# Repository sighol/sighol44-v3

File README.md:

# Sighol-44 v3

# Installation

Install both `kicad` and `kicad-library` from the OS package repository.

Remember to add the [marbastlib](https://github.com/ebastler/marbastlib) symbol and footprints library.
Check the github page for installation instructions.

Also install the `Fabrication toolkit` from the official KiCad repository.
Search for `JLC` in the plugins tab.

# Inkscape edge cut tutorial

## Export SVG from KiCad
- In KiCad, *File* -> *Print*
- Select the Fab, Silkscreen, and User.Drawings layers.
- Then print as SVG

## Convert SVG to Bitmap to make it easier to work with. (optional)
- Open the SVG in inkscape.
- Open Edit ->, Preference, and select the *Imported Images* tab.
- Change the Craete resolution to about 500 dpi and close the preferences window.
- Then select (S) the white background and delete it.
- Then select (S) everything else.
- Click on Edit -> Make a Bitmap copy.
- Then move the bitmap copy to the center of the screen and delete all the other paths

Another alternative is to create a new layer, and move all the paths into this layer.
Snapping will work better when drawing the initial bezier curve, but I don't think it is worth it.

## Draw outline

- Use the **Pen Tool** (B) to draw an outline around the board. Use straight lines.b
- Hold down CTRL to draw straight lines.
- Move around the canvas by holding down the middle mouse button.
- After you have completed the outline, you can use the Node Tool (N) to delete nodes that are redundant. Select the node and use the **Delete** key.
- Delete bezier curve handles by holding control and left clicking on them.
- Add bezier curve handles by holding control and left clicking on a node.
- Double click on the curve to add a new node.
- Show the bezier handles by toggling a button to the right of the X and Y text boxes.
- The X and Y text boxes can also be used to place the nodes.

## Path effects
- Make sure none of the nodes have bezier curve handles.
- First create an offset of around 1mm.
- Then create a corner of around 1mm.
- Then you can customize the corners using the Node Tool (N).
- Make sure the radiuses you customize are symmetric and equal. You _will_ notice.
- For the thumb keys, it is best to have the biggest possible radius (to the center of the switch).

## Exporting SVG for KiCad

- File -> Export (Ctrl+Shift+E)
- Select the output directory and file. Should be `output_export.svg`.
- Toggle **Export Selected Only**.
- Select the outline (S).
- Click on the **Export** button.

## Import into KiCad

- File -> Import -> Graphics
- Use Import scale 1.33 and set layer to Edge.Cuts, and click OK.
- It is useful to select the outline and press M to move it around using the arrow keys. Press ENTER to confirm.
- You will have to iterate. If you create a big fill zone (select F.Cu and fill with ground), and then fill with **B**, you can use that as a guide when deleting and adding back the new edge cut.
- Alternatively, after placing it, notice

It is easy to place the new export on the of the previous export and then delete the previous, for placement.

## Tips and tricks with design

- The bigger the outline, the easier it will be to place rubber feet so that it doesn't wobble.
- Place the grid on the top-left key. `Place` -> `Grid`.
- Guideline: Horizontal traces are blue. Vertical traces are red.
- In **PCB Editor**:
    - F8 to apply from schematics
    - B to build fill zones.
    - Ctrl+Shift+F to import graphics.
    - Top Copper **PgUp**
    - Bottom Copper **PgDown**
    - V: Toggle top and bottom copper layer
    - Tools -> Update Footprints from Library: Take them all!
    - Text fields support [variables substitiution](https://docs.kicad.org/master/id/eeschema/eeschema_advanced.html#:~:text=KiCad%20supports%20text%20variables%2C%20which,schematic%20or%20board%20setup%20dialogs.)
    - D: Drag component line or track. (You can also drag the tracks.)
    - G: Drag component node or track.

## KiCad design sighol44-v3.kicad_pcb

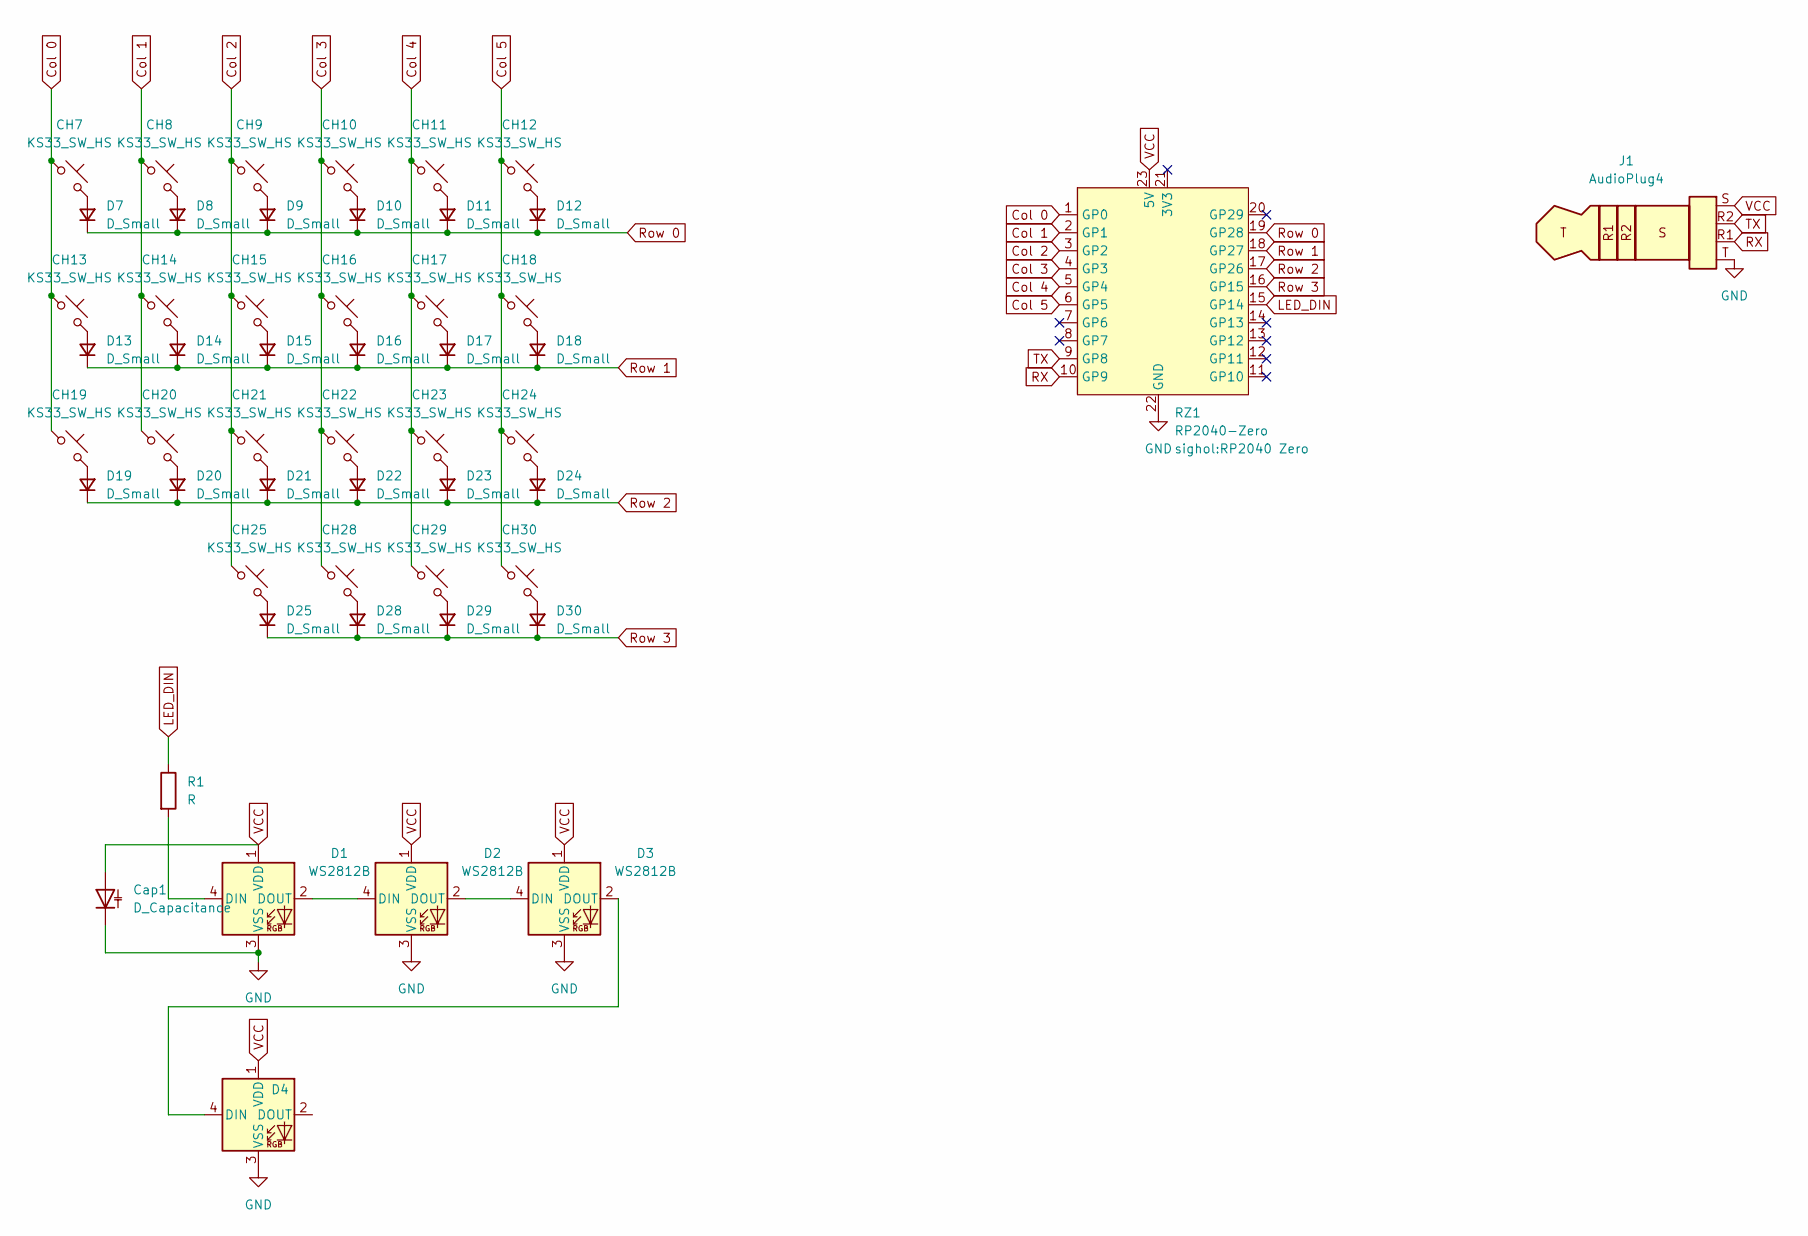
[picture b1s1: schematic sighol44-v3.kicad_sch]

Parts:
CH7, CH8, CH9, CH10, CH11, CH12, CH13, CH14, CH15, CH16, CH17, CH18, CH19, CH20, CH21, CH22, CH23, CH24, CH25, CH28, CH29, CH30: KS33_SW_HS; Kailh_socket_PG1350 reversible HS-only
Cap1: D_Capacitance; CP_Radial_D5.0mm_P2.00mm
D1, D2, D3, D4: WS2812B; LED_WS2812B_PLCC4_5.0x5.0mm_P3.2mm_reversible
D7, D8, D9, D10, D11, D12, D13, D14, D15, D16, D17, D18, D19, D20, D21, D22, D23, D24, D25, D28, D29, D30: D_Small; D_DO-35_SOD27_P7.62mm_Horizontal
J1: AudioPlug4; TRRS-PJ-320A
R1: R; R_Axial_DIN0207_L6.3mm_D2.5mm_P7.62mm_Horizontal
RZ1: RP2040-Zero; RP2040 Zero

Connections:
Col 0: CH7.1, CH13.1, CH19.1, RZ1.1 (GP0)
Col 1: CH8.1, CH14.1, CH20.1, RZ1.2 (GP1)
Col 2: CH9.1, CH15.1, CH21.1, CH25.1, RZ1.3 (GP2)
Col 3: CH10.1, CH16.1, CH22.1, CH28.1, RZ1.4 (GP3)
Col 4: CH11.1, CH17.1, CH23.1, CH29.1, RZ1.5 (GP4)
Col 5: CH12.1, CH18.1, CH24.1, CH30.1, RZ1.6 (GP5)
GND: Cap1.1 (K), D1.3 (VSS), D2.3 (VSS), D3.3 (VSS), D4.3 (VSS), J1.T, RZ1.22 (GND)
LED_DIN: R1.1, RZ1.15 (GP14)
unnamed: D1.4 (DIN), R1.2
unnamed: D1.2 (DOUT), D2.4 (DIN)
unnamed: D2.2 (DOUT), D3.4 (DIN)
unnamed: D3.2 (DOUT), D4.4 (DIN)
unnamed: CH7.2, D7.2 (A)
unnamed: CH8.2, D8.2 (A)
unnamed: CH9.2, D9.2 (A)
unnamed: CH10.2, D10.2 (A)
unnamed: CH11.2, D11.2 (A)
unnamed: CH12.2, D12.2 (A)
unnamed: CH13.2, D13.2 (A)
unnamed: CH14.2, D14.2 (A)
unnamed: CH15.2, D15.2 (A)
unnamed: CH16.2, D16.2 (A)
unnamed: CH17.2, D17.2 (A)
unnamed: CH18.2, D18.2 (A)
unnamed: CH19.2, D19.2 (A)
unnamed: CH20.2, D20.2 (A)
unnamed: CH21.2, D21.2 (A)
unnamed: CH22.2, D22.2 (A)
unnamed: CH23.2, D23.2 (A)
unnamed: CH24.2, D24.2 (A)
unnamed: CH25.2, D25.2 (A)
unnamed: CH28.2, D28.2 (A)
unnamed: CH29.2, D29.2 (A)
unnamed: CH30.2, D30.2 (A)
RX: J1.R1, RZ1.10 (GP9)
Row 0: D7.1 (K), D8.1 (K), D9.1 (K), D10.1 (K), D11.1 (K), D12.1 (K), RZ1.19 (GP28)
Row 1: D13.1 (K), D14.1 (K), D15.1 (K), D16.1 (K), D17.1 (K), D18.1 (K), RZ1.18 (GP27)
Row 2: D19.1 (K), D20.1 (K), D21.1 (K), D22.1 (K), D23.1 (K), D24.1 (K), RZ1.17 (GP26)
Row 3: D25.1 (K), D28.1 (K), D29.1 (K), D30.1 (K), RZ1.16 (GP15)
TX: J1.R2, RZ1.9 (GP8)
VCC: Cap1.2 (A), D1.1 (VDD), D2.1 (VDD), D3.1 (VDD), D4.1 (VDD), J1.S, RZ1.23 (5V)

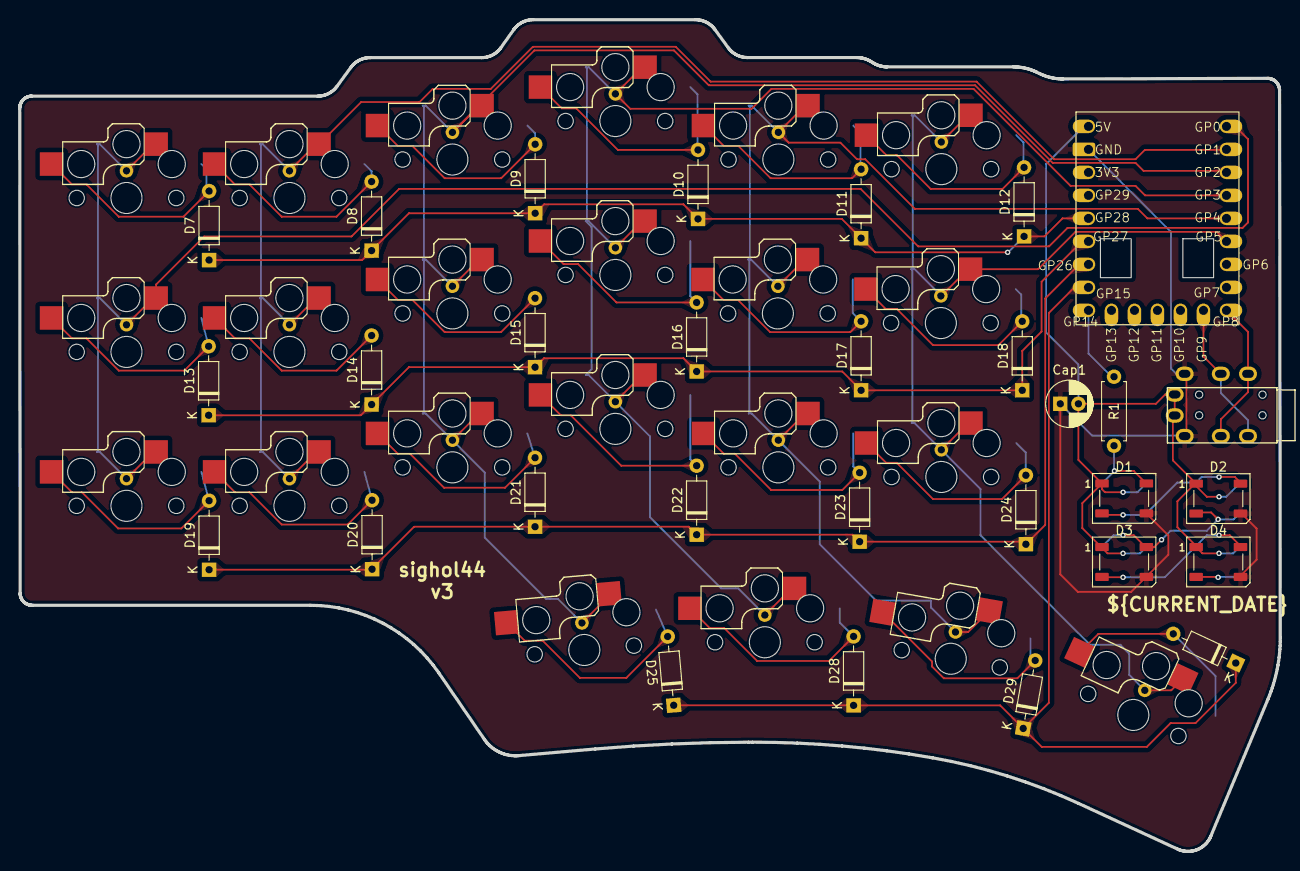
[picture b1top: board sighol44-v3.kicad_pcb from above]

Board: 2 copper layers, 139.2 x 91.9 mm, 52 parts (0 on the bottom side), 41 nets.

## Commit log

2025-04-25 Add edge cut and add tutorial to README
2025-04-25 Thicker outline and more traces
2025-04-25 Complete most traces (not LEDs)
2025-04-25 pcb in readme
2025-04-25 Try to fix LEDs. All checks succeed
2025-04-25 Updatte RP2040 Zero footprint with silkscreen border
2025-04-25 LED footprint + current_date
2025-04-25 render + paint capacitor on back silk
2025-04-25 Moved tracks around using D and G
2025-04-25 Move traces around and make some footprints more pretty. Resistor is more pretty
2025-04-25 pcb.png
2025-04-25 More track movements
2025-04-26 Move some tracks around again
2025-04-27 Move D30 diode so that a rubbe foot can be placed bottom right
2025-04-28 Align LEDs
2025-04-29 Rename to sighol44-v3
2025-04-29 Fat outline (2mm)
2025-04-29 Remove circle and move some tracks
2025-04-29 Remove GND Vias. Fill islands instead
2025-04-29 Move bottom right diode + other minor changes
2025-04-29 Ready for manufacturing
2025-04-29 Add QMK settings
2025-06-04 Disable USB startup check and disable rgb split
2025-07-02 COMBO_TERM 100
2025-08-28 Disable COMBO_TERM
2025-10-30 Remove COMBO, and use chordal tap instead
2025-10-31 cleanup + make Makefile more robust
2025-10-31 @ and $
2025-10-31 alignment
2025-11-01 Add comma and dot to quick numbers
2025-11-17 quick_numbers: add comman and dot
2026-02-17 Fix send_string_rewrite and add reviewable button
2026-04-01 one shot key for right ctrl
2026-04-28 Try to fix the dead-until-reset-on-startup bug
